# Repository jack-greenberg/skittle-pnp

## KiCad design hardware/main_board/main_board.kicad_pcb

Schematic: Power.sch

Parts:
C201, C202: C_10uF+; T491C105K050AT; MPN 718-TR3C106K016C0500CT-ND
R201: R_100; R_0805_OEM; MPN RNCP0805FTD100RCT-ND
R202: R_500
R203: R_200; R_0805_OEM; MPN RMCF0805JT200RCT-ND
TP201: 3.3_LED; Test_Point_SMD
TP202: 3.3_LED_GND; Test_Point_SMD
TP203: 12V_LED; Test_Point_SMD
TP204: 12V_LED_GND; Test_Point_SMD
TP205: 5V_LED; Test_Point_SMD
TP206: 5V_LED_GND; Test_Point_SMD
U201: LM1117-5.0

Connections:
+5V: C202.1, R203.1, U201.2 (VO); also elsewhere on the board
GND: C201.2, C202.2, TP202.1, TP204.1, TP206.1, U201.1 (GND); also elsewhere on the board
unnamed: R201.2, TP201.1
unnamed: R203.2, TP205.1
unnamed 50: TP203.1; also elsewhere on the board
PWR_SW_OFF: C201.1, R201.1, U201.3 (VI); also elsewhere on the board

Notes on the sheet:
12V - 5V Linear Regulator
Power Switch (and ESTOP)
Off Side of Power Switch
On Side of Power Switch
12V from the power supply
Solder the LED wires onto the exposed copper
min 65 Ohms
3.3V Indicator LED
solder the LED wires to the exposed copper
change caps to this: https://www.vishay.com/docs/40080/tr3.pdf
min 150 Ohm resistor

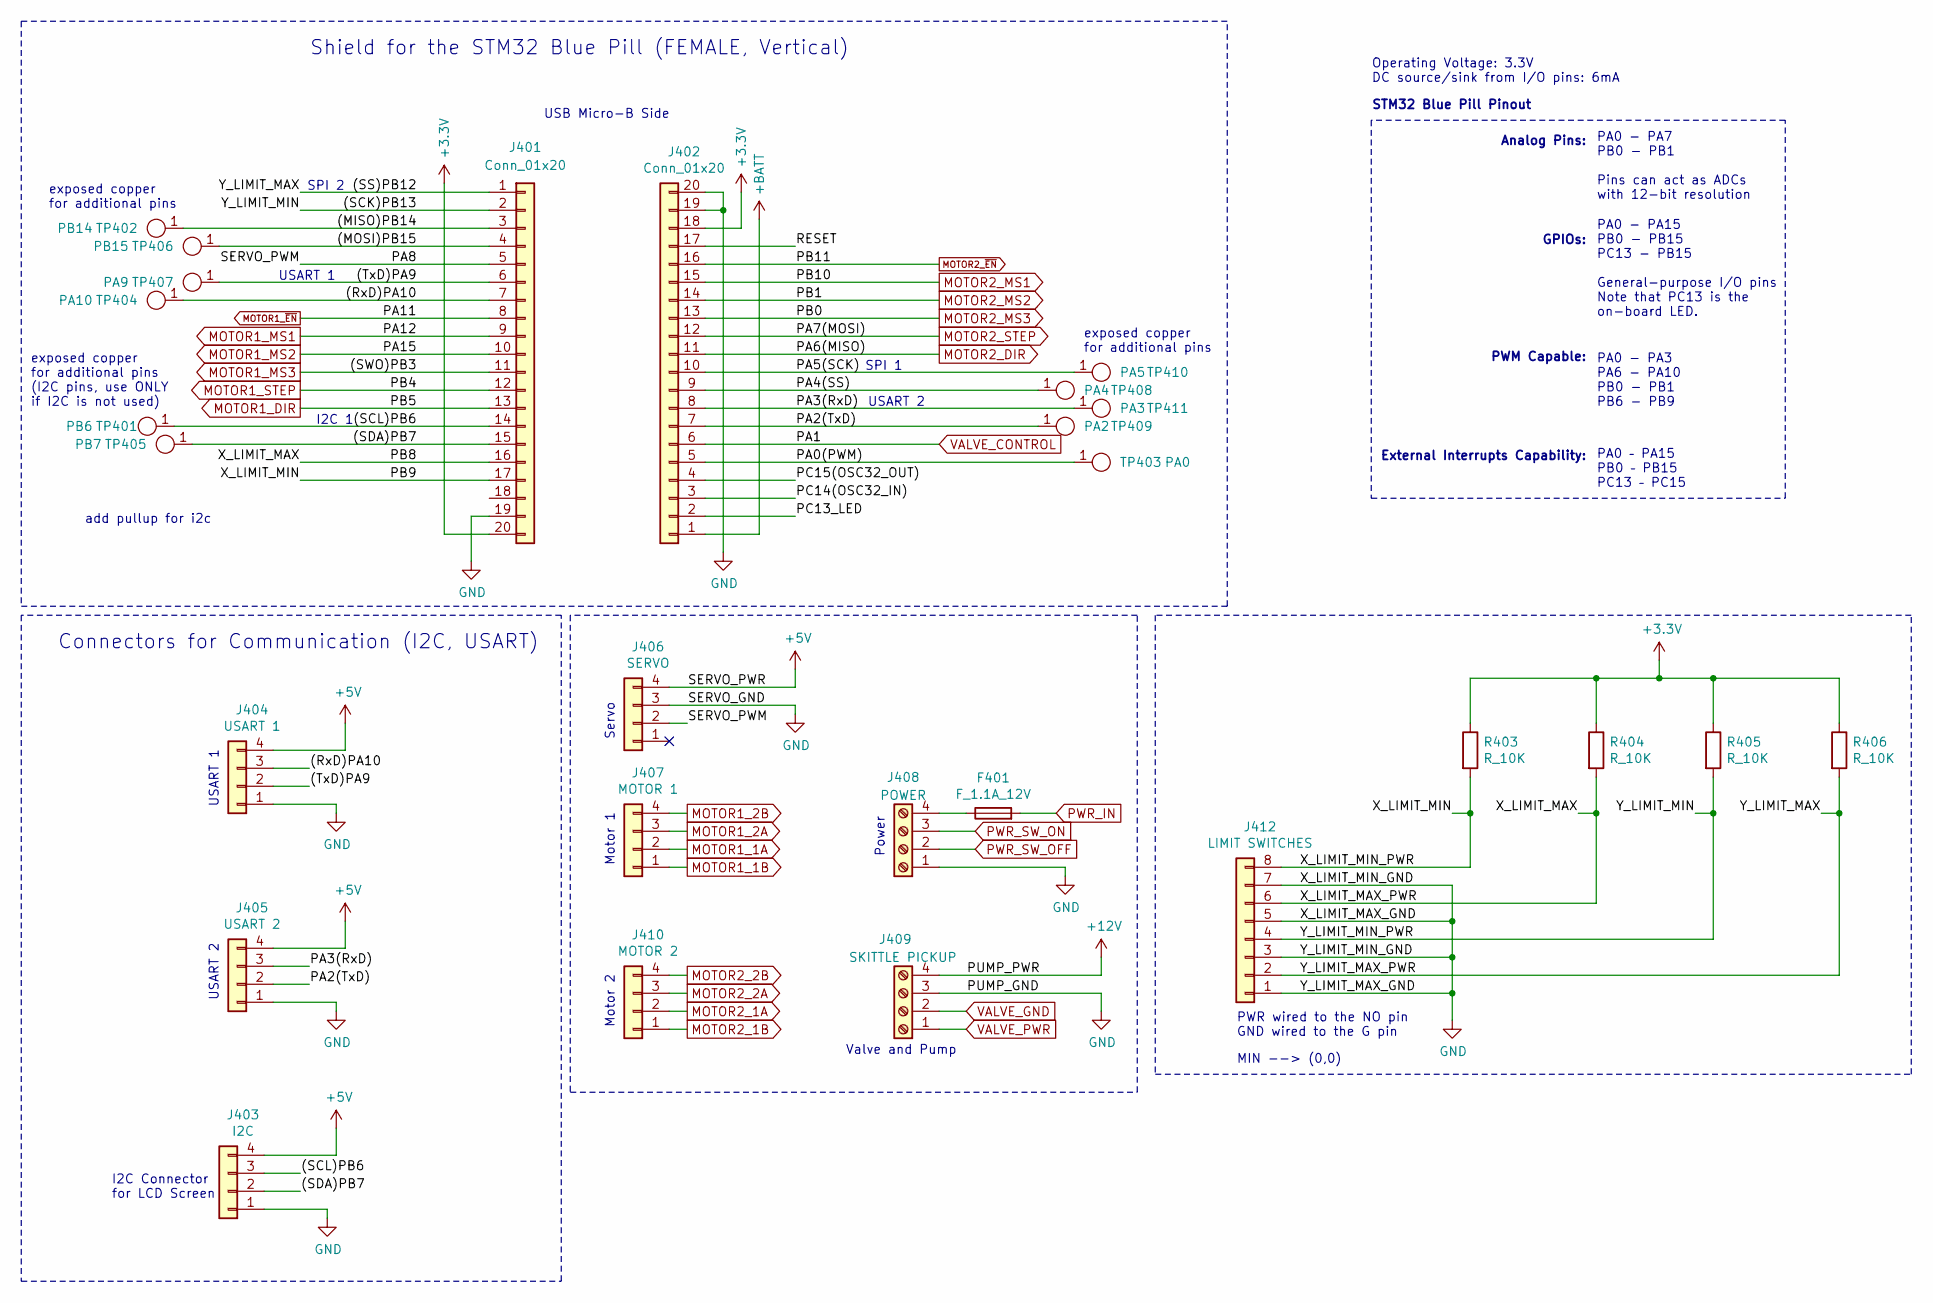
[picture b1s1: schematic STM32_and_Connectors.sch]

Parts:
F401: F_1.1A_12V; 1206L075SLYR; MPN F5764CT-ND
J401, J402: Conn_01x20; RHDR20W80P0X254_1X20_5130X254X880P
J403: I2C; SULLINS_PPTC041LFBN-RC
J404: USART 1; SULLINS_PPTC041LFBN-RC
J405: USART 2; SULLINS_PPTC041LFBN-RC
J406: SERVO; SULLINS_PPTC041LFBN-RC
J407: MOTOR 1; SULLINS_PPTC041LFBN-RC
J408: POWER; CUI_TB006-508-04BE
J409: SKITTLE PICKUP; CUI_TB006-508-04BE
J410: MOTOR 2; SULLINS_PPTC041LFBN-RC
J412: LIMIT SWITCHES; RHDR8W80P0X254_1X8_2082X254X850P
R403, R404, R405, R406: R_10K; R_0805_OEM; MPN CRS0805-FX-1002ELFCT-ND
TP401: PB6; Test_Point_SMD
TP402: PB14; Test_Point_SMD
TP403: PA0; Test_Point_SMD
TP404: PA10; Test_Point_SMD
TP405: PB7; Test_Point_SMD
TP406: PB15; Test_Point_SMD
TP407: PA9; Test_Point_SMD
TP408: PA4; Test_Point_SMD
TP409: PA2; Test_Point_SMD
TP410: PA5; Test_Point_SMD
TP411: PA3; Test_Point_SMD

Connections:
+3V3: J401.20, J402.18, R403.1, R404.1, R405.1, R406.1; also elsewhere on the board
+5V: J401.18, J403.4, J404.4, J405.4, J406.4; also elsewhere on the board
+BATT: J402.1
/STM32_and_Connectors/(MISO)PB14: J401.3, TP402.1
/STM32_and_Connectors/(MOSI)PB15: J401.4, TP406.1
/STM32_and_Connectors/(RxD)PA10: J401.7, J404.3, TP404.1
/STM32_and_Connectors/(SCK)PB13: J401.2, J412.4, R405.2
/STM32_and_Connectors/(SCL)PB6: J401.14, J403.3, TP401.1
/STM32_and_Connectors/(SDA)PB7: J401.15, J403.2, TP405.1
/STM32_and_Connectors/(SS)PB12: J401.1, J412.2, R406.2
/STM32_and_Connectors/(TxD)PA9: J401.6, J404.2, TP407.1
/STM32_and_Connectors/PA0(PWM): J402.5, TP403.1
/STM32_and_Connectors/PA2(TxD): J402.7, J405.2, TP409.1
/STM32_and_Connectors/PA3(RxD): J402.8, J405.3, TP411.1
/STM32_and_Connectors/PA4(SS): J402.9, TP408.1
/STM32_and_Connectors/PA5(SCK): J402.10, TP410.1
/STM32_and_Connectors/PA8: J401.5, J406.2
/STM32_and_Connectors/PB8: J401.16, J412.6, R404.2
/STM32_and_Connectors/PB9: J401.17, J412.8, R403.2
/STM32_and_Connectors/PC13_LED: J402.2
/STM32_and_Connectors/PC14(OSC32_IN): J402.3
/STM32_and_Connectors/PC15(OSC32_OUT): J402.4
/STM32_and_Connectors/RESET: J402.17
GND: J401.19, J402.19, J402.20, J403.1, J404.1, J405.1, J406.3, J408.1, J409.3, J412.1, J412.3, J412.5, J412.7; also elsewhere on the board
MOTOR1_1A: J407.2; also elsewhere on the board
MOTOR1_1B: J407.1; also elsewhere on the board
MOTOR1_2A: J407.3; also elsewhere on the board
MOTOR1_2B: J407.4; also elsewhere on the board
MOTOR1_DIR: J401.13; also elsewhere on the board
MOTOR1_MS1: J401.9; also elsewhere on the board
MOTOR1_MS2: J401.10; also elsewhere on the board
MOTOR1_MS3: J401.11; also elsewhere on the board
MOTOR1_STEP: J401.12; also elsewhere on the board
MOTOR1_~EN: J401.8; also elsewhere on the board
MOTOR2_1A: J410.2; also elsewhere on the board
MOTOR2_1B: J410.1; also elsewhere on the board
MOTOR2_2A: J410.3; also elsewhere on the board
MOTOR2_2B: J410.4; also elsewhere on the board
MOTOR2_DIR: J402.11; also elsewhere on the board
MOTOR2_MS1: J402.15; also elsewhere on the board
MOTOR2_MS2: J402.14; also elsewhere on the board
MOTOR2_MS3: J402.13; also elsewhere on the board
MOTOR2_STEP: J402.12; also elsewhere on the board
MOTOR2_~EN: J402.16; also elsewhere on the board
unnamed: F401.1, J408.4
PWR_SW_OFF: J408.2, J409.1, J409.4; also elsewhere on the board
VALVE_CONTROL: J402.6; also elsewhere on the board
VALVE_GND: J409.2; also elsewhere on the board

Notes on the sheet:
Shield for the STM32 Blue Pill (FEMALE, Vertical)
USB Micro-B Side
PA0 - PA7 PB0 - PB1 Pins can act as ADCs with 12-bit resolution
Analog Pins:
GPIOs:
PA0 - PA15 PB0 - PB15 PC13 - PB15 General-purpose I/O pins Note that PC13 is the on-board LED.
PWM Capable:
PA0 - PA3 PA6 - PA10 PB0 - PB1 PB6 - PB9
External Interrupts Capability:
PA0 – PA15 PB0 – PB15 PC13 – PC15
STM32 Blue Pill Pinout
USART 1
SPI 1
SPI 2
Operating Voltage: 3.3V DC source/sink from I/O pins: 6mA
I2C 1
USART 2
I2C Connector for LCD Screen
exposed copper for additional pins
exposed copper for additional pins (I2C pins, use ONLY if I2C is not used)
Connectors for Communication (I2C, USART)
PWR wired to the NO pin GND wired to the G pin
MIN --> (0,0)
add pullup for i2c
Motor 2
Motor 1
Servo
Power
Valve and Pump

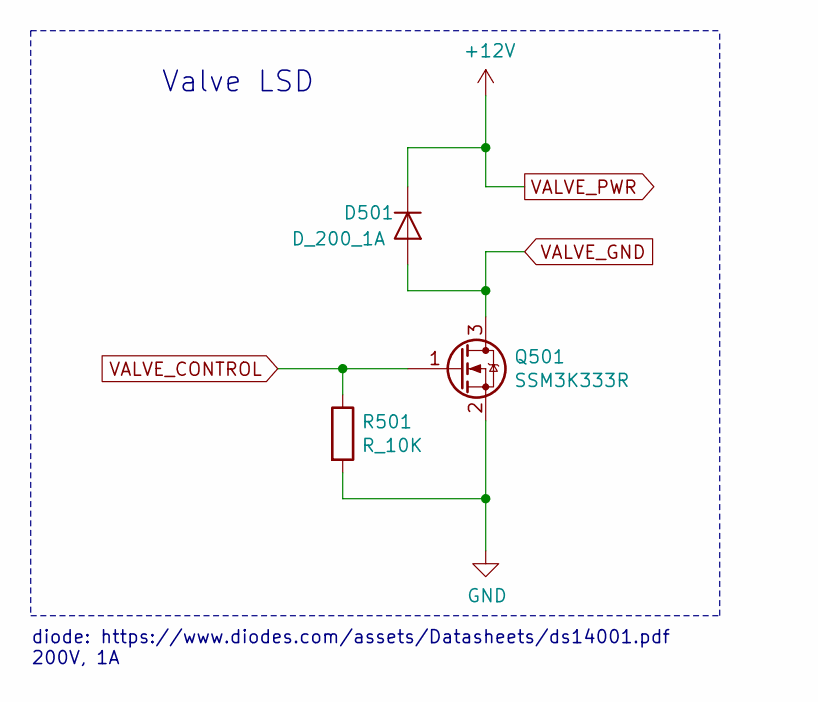
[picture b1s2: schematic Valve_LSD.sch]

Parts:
D501: D_200_1A; DIOM5226X240N
Q501: SSM3K333R; SOT-23F; MPN SSM3K333RLFCT-ND
R501: R_10K; R_0805_OEM; MPN CRS0805-FX-1002ELFCT-ND

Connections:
GND: Q501.2 (S), R501.2; also elsewhere on the board
PWR_SW_OFF: D501.1 (K); also elsewhere on the board
VALVE_CONTROL: Q501.1 (G), R501.1; also elsewhere on the board
VALVE_GND: D501.2 (A), Q501.3 (D); also elsewhere on the board

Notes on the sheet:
Valve LSD
diode: https://www.diodes.com/assets/Datasheets/ds14001.pdf 200V, 1A

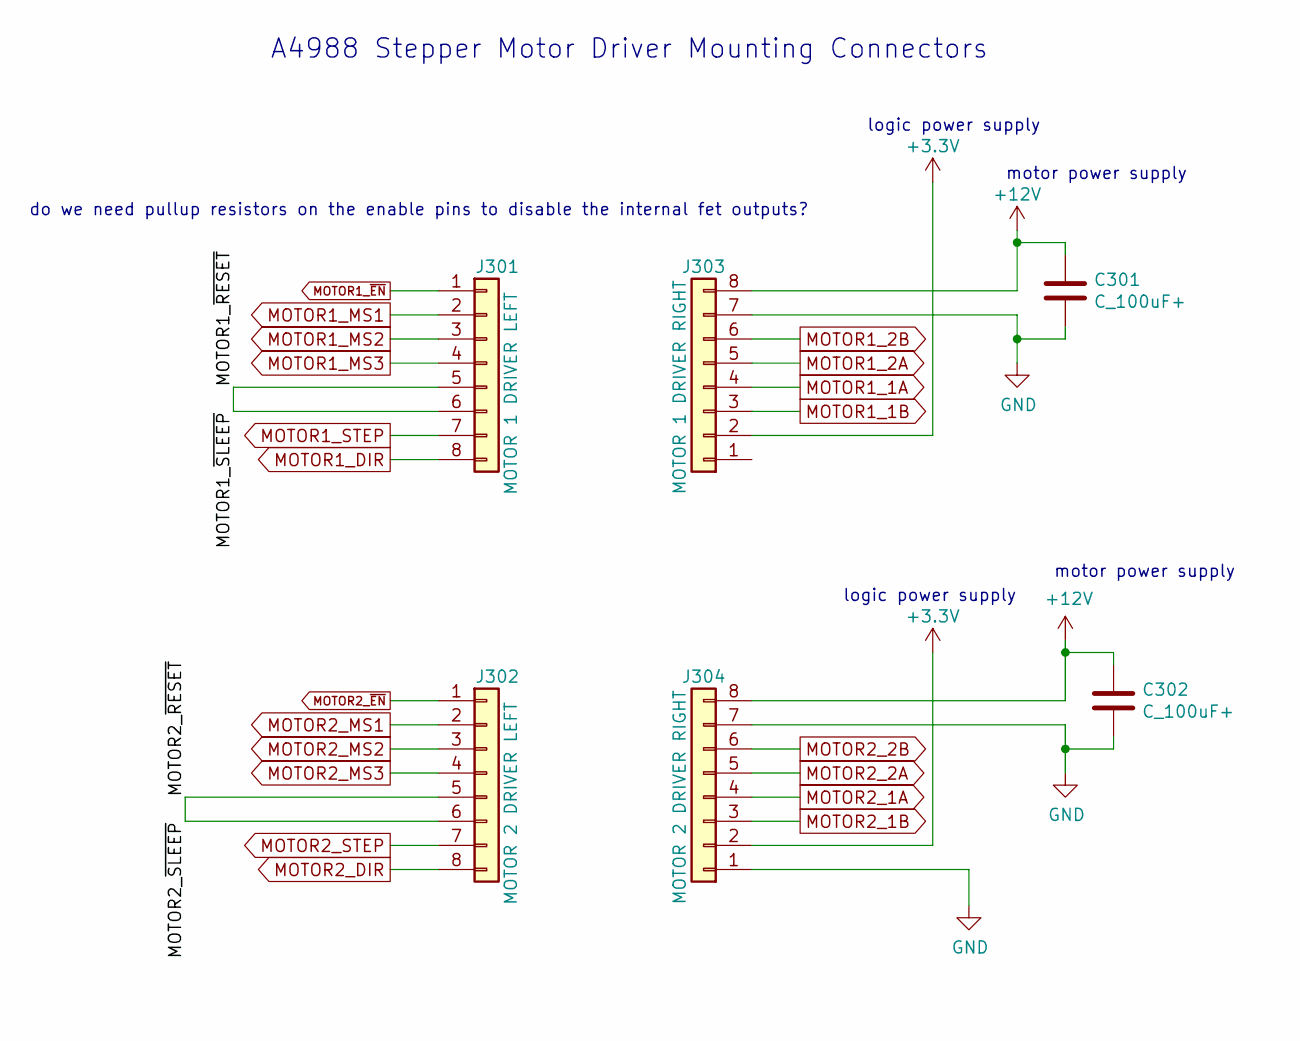
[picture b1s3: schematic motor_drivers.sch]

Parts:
C301, C302: C_100uF+
J301: MOTOR 1 DRIVER LEFT
J302: MOTOR 2 DRIVER LEFT
J303: MOTOR 1 DRIVER RIGHT
J304: MOTOR 2 DRIVER RIGHT

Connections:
+3V3: J303.2, J304.2; also elsewhere on the board
/Motor Drivers/MOTOR1_~RESET: J301.5, J301.6
/Motor Drivers/MOTOR2_~RESET: J302.5, J302.6
GND: C301.1, C302.1, J303.1, J303.7, J304.1, J304.7; also elsewhere on the board
MOTOR1_1A: J303.4; also elsewhere on the board
MOTOR1_1B: J303.3; also elsewhere on the board
MOTOR1_2A: J303.5; also elsewhere on the board
MOTOR1_2B: J303.6; also elsewhere on the board
MOTOR1_DIR: J301.8; also elsewhere on the board
MOTOR1_MS1: J301.2; also elsewhere on the board
MOTOR1_MS2: J301.3; also elsewhere on the board
MOTOR1_MS3: J301.4; also elsewhere on the board
MOTOR1_STEP: J301.7; also elsewhere on the board
MOTOR1_~EN: J301.1; also elsewhere on the board
MOTOR2_1A: J304.4; also elsewhere on the board
MOTOR2_1B: J304.3; also elsewhere on the board
MOTOR2_2A: J304.5; also elsewhere on the board
MOTOR2_2B: J304.6; also elsewhere on the board
MOTOR2_DIR: J302.8; also elsewhere on the board
MOTOR2_MS1: J302.2; also elsewhere on the board
MOTOR2_MS2: J302.3; also elsewhere on the board
MOTOR2_MS3: J302.4; also elsewhere on the board
MOTOR2_STEP: J302.7; also elsewhere on the board
MOTOR2_~EN: J302.1; also elsewhere on the board
PWR_SW_OFF: C301.2, C302.2, J303.8, J304.8; also elsewhere on the board

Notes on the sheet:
A4988 Stepper Motor Driver Mounting Connectors
logic power supply
motor power supply
do we need pullup resistors on the enable pins to disable the internal fet outputs?

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
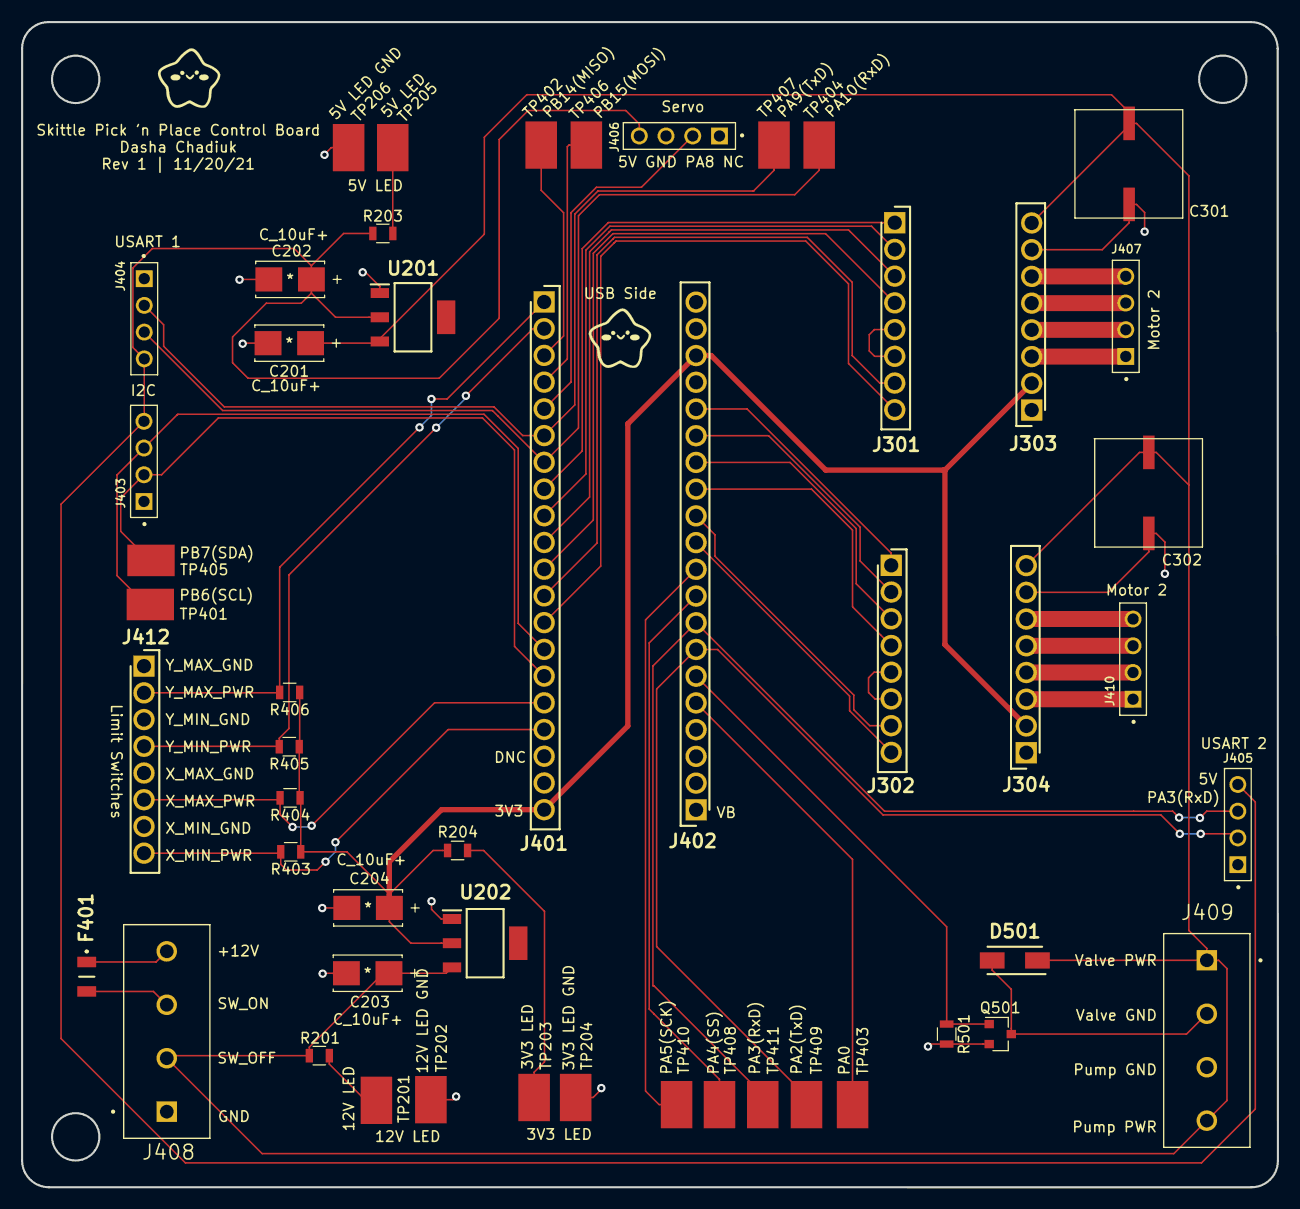
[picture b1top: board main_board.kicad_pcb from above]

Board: 2 copper layers, 119.4 x 110.7 mm, 51 parts (0 on the bottom side), 49 nets.

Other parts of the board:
C203, C204: C_10uF+; T491C105K050AT
R204: R_200; R_0805_OEM
U202: LM1117-3.3; SOT230P700X180-4N

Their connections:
+3V3: C204.1, R204.1, U202.2; also elsewhere on the board
GND: C203.2, C204.2, U202.1; also elsewhere on the board
unnamed 50: R204.2; also elsewhere on the board
PWR_SW_OFF: C203.1, U202.3; also elsewhere on the board

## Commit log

2021-10-27 Add preliminary image processing script
2021-10-28 Add initial firmware files
2021-10-28 Remove firmware as submodule
2021-10-28 Add external libraries as submodules
2021-10-28 Fix toolchain
2021-11-02 Add initial prototype 1 code
2021-11-03 Add sprint 1 motion control
2021-11-03 Add GCode parser
2021-11-03 Add error checking for parser
2021-11-03 Fix command/wait for ok order
2021-11-14 Add firmware application structure and movement algorithm
2021-11-17 completed main interface board
2021-11-17 changed order of servo connections
2021-11-17 Flesh out GCode parser
2021-11-17 fixed valve lsd circuit
2021-11-17 added connector for powering limit switches
2021-11-17 Add image processing and movement protocol
2021-11-17 Use most up-to-date image processing code
2021-11-17 Use the most current image processing script
2021-11-17 Add 500us timer integration
2021-11-17 Added skittle_pnp symbol and footprint library
    Added 10uF tantalum capacitor and diode to the
    skittle_pnp symbol and footprints libraries.
2021-11-30 Add linear slope motion algo
2021-12-01 Fix EXTI interrupts for limit switches
2021-12-01 Fix movement and add homing command
2021-12-03 Integrate servo code
2021-12-03 final schematic and layout
2021-12-03 Update with new pins
2021-12-04 Fix (hopefully) EXTI interrupts
2021-12-08 added step file for pcb
2021-12-11 Add servo structs and tweak speeds
2021-12-12 Update PWM pins
2021-12-13 Add working python script and sample image
2021-12-13 added final schematic and layout
2021-12-13 Add final code files

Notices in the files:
parts and their libraries:
Copyright 2021 Accelerated Designs. All rights reserved.
